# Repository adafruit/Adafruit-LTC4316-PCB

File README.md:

## Adafruit LTC4316 I2C Address Translator - Stemma QT / Qwiic PCB

<a href="http://www.adafruit.com/products/5914"><br/>
Click here to purchase one from the Adafruit shop</a>

PCB files for the Adafruit LTC4316 I2C Address Translator - Stemma QT / Qwiic. 

Format is EagleCAD schematic and board layout
* https://www.adafruit.com/product/5914

### Description

Adafruit has hundreds of designs that use I2C - a two-wire protocol that can let you quickly connect sensors, OLEDs, GPIO expanders, and more. Folks love I2C because you can simply connect 4 wires for power and data, and even better, share those wires with multiple devices!

One things folks don't like about I2C is that each device requires it's own unique 'address'. You can only have one device with a 0x20 address, for example, so while in theory you could have up to 127 device, each for the 7-bits of address space available, in reality you will quickly bump into two sensors with the same address. Many I2C components have jumpers or switches that allow changing the address, but not all. And some only let you pick between two values. One solution is to use an I2C multiplexer,  and these work pretty well, but they require some noodling in your code to set up the 'plexer and then switch between the devices being plexed.

The Adafruit LTC4316 I2C Address Translator is another solution, with some magic sprinkled inside. This chip does on the fly address translation. There's an 'input I2C' half, and an 'output I2C' half. And any devices on the 'output' half will automatically have their addresses translated from the input half. Specifically, each device will have bit A6 flipped  (most-significant-bit of the address) and then bits A4 and A5 can also be flipped or kept the same, with the two DIP switches on board. To determine the translated address, we use XOR bitwise math.

OK that's a little confusing so let's work through an example. Say we have an AHT20 connected on the output side of this breakout. The AHT20 does not have an adjustable I2C address: it's fixed at 0x38. If both DIP switches are ON, then only A6 is flipped. That means the I2C controller on the input side will see 0x38 XOR 0x40 = 0x78 address. If we flip the A5 switch off, now it will be 0x38 XOR 0x60 = 0x58 and if both switches are off, now bits A4, A5 and A6 will be flipped, so 0x38 XOR 0x70 = 0x48. As far as the AHT20 is concerned, it will happily still see I2C writes and reads on 0x38, but from the I2C controller's perspective, the device is responding on the new address.

If you need more than 4 address translation options (two switches give you 4 options) we also have a spot where you can solder an XOR_LOW resistor for setting the 'bottom' 3 bits by soldering in a resistor value according to the datasheet. It can get confusing quickly so we definitely recommend using an I2C scanner to debug. Note also that you have to reset the LTC if you change the translation address with resistors or the DIP switches: the translation value is picked up on chip boot and isn't on-the-fly adjustable without a toggle of the Enable pin.

While this chip is magical, there's a few things to watch for: it doesn't seem to support clock-stretching so not for funky chips like BNO055. Just because you can change the address on the fly, doesn't mean the drive supports it! Some firmware is expecting a specific address and it may not be trivial to change the address. Check the driver to make sure you know how to change the address, to the new value.

To get you going fast, we spun up a custom-made PCB in the STEMMA QT form factor, making it easy to interface. The STEMMA QT connectors on either side are compatible with the SparkFun Qwiic I2C connectors. This allows you to make solderless connections between your development board and the LTC4316 or to chain it with a wide range of other sensors and accessories using a compatible cable. QT Cable is not included, but we have a variety in the shop. 

### License

Adafruit invests time and resources providing this open source design, please support Adafruit and open-source hardware by purchasing products from [Adafruit](https://www.adafruit.com)!

Designed by Limor Fried/Ladyada for Adafruit Industries.

Creative Commons Attribution/Share-Alike, all text above must be included in any redistribution. 
See license.txt for additional details.

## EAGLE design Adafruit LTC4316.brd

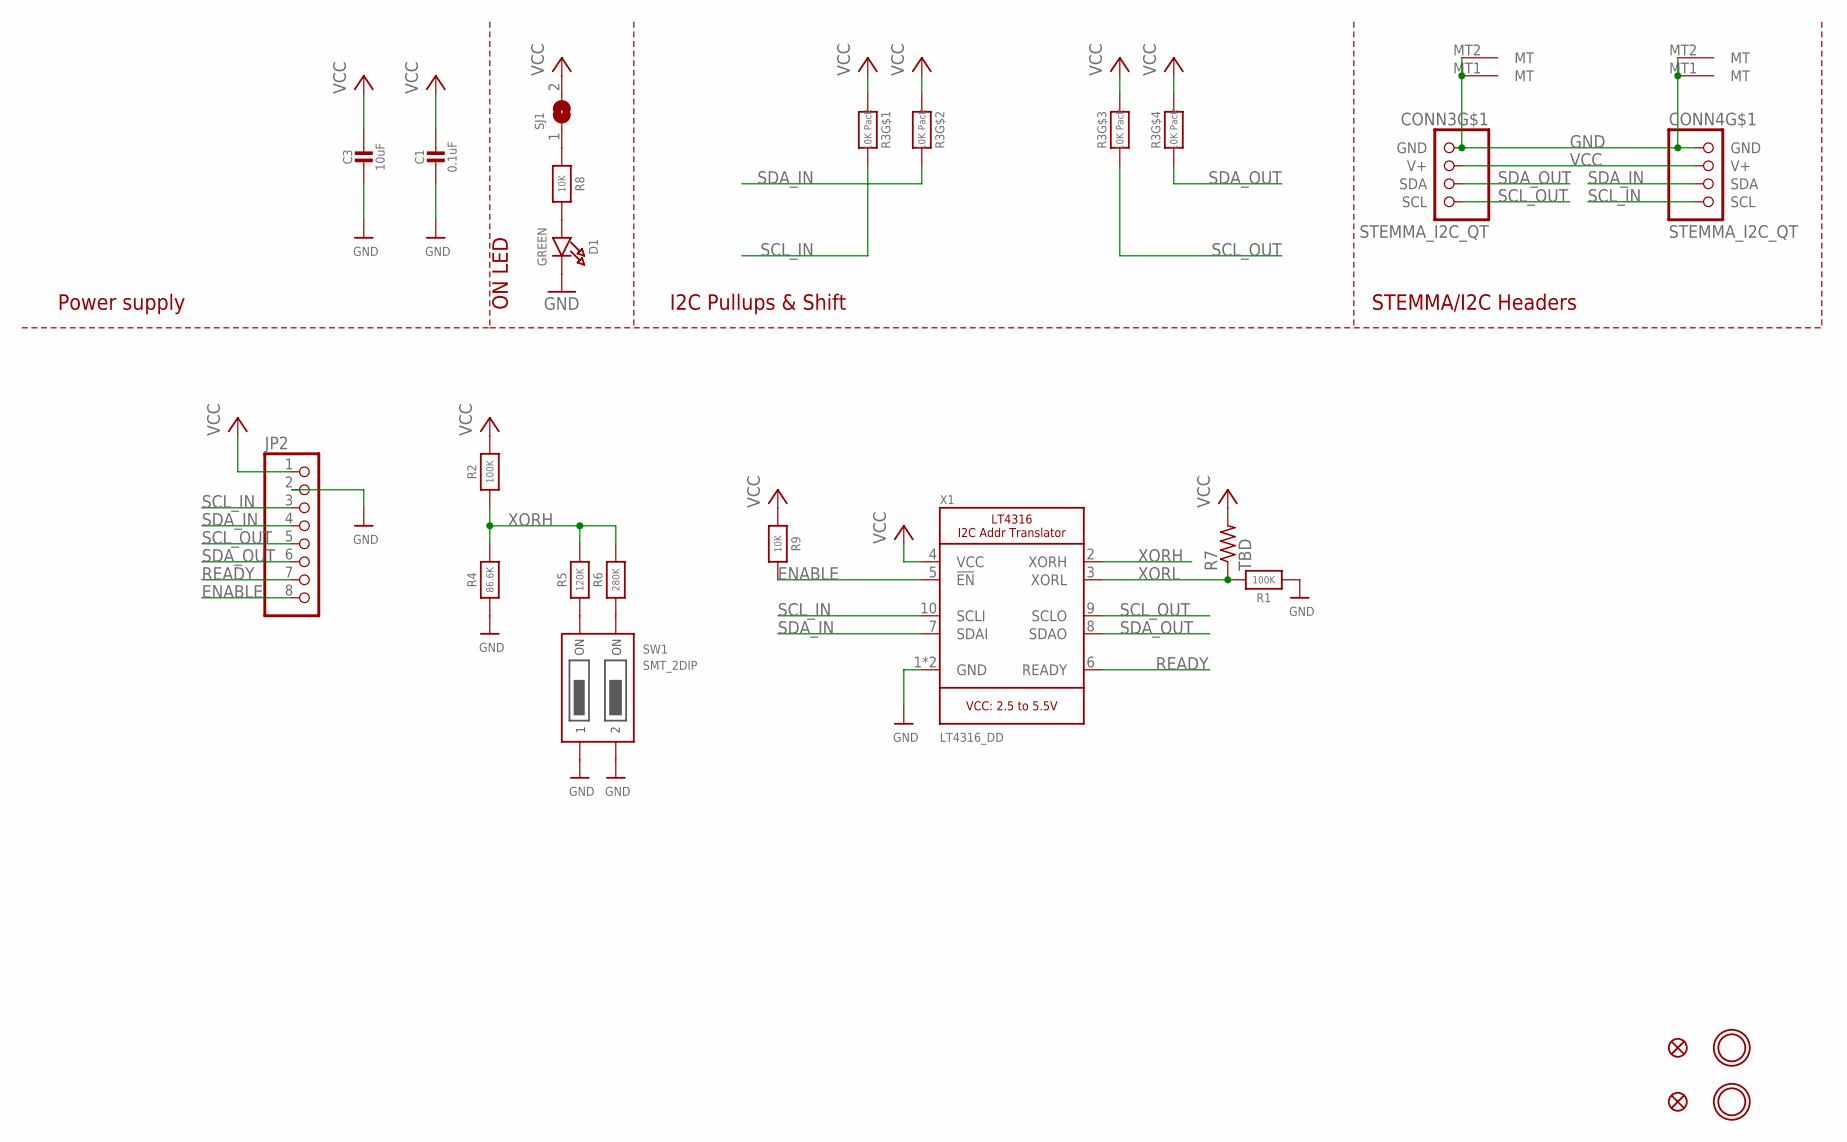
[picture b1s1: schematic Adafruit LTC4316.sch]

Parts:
C1: 0.1uF; 0603-NO
C3: 10uF; 0805-NO
CONN3, CONN4: STEMMA_I2C_QT; JST_SH4
D1: GREEN; CHIPLED_0603_NOOUTLINE
FID3, FID4: FIDUCIAL_1MM
JP2: HEADER-1X870MIL; 1X08_ROUND_70
R1, R2: 100K; 0603-NO
R3: 10K Pack; RESPACK_4X0603
R4: 86.6K; 0603-NO
R5: 120K; 0603-NO
R6: 280K; 0603-NO
R7: TBD; 0204/7
R8, R9: 10K; 0603-NO
SJ1: SOLDERJUMPERCLOSED; SOLDERJUMPER_CLOSEDWIRE
SW1: SMT_2DIP; DIPSWITCH_2PIN
U$1, U$17: MOUNTINGHOLE2.5; MOUNTINGHOLE_2.5_PLATED
X1: LT4316_DD; DFN10_3X3MM

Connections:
ENABLE: JP2.8, R9.2, X1.5 (!EN)
GND: C1.2, C3.2, CONN3.1 (GND), CONN3.MT1 (MT), CONN3.MT2 (MT), CONN4.1 (GND), CONN4.MT1 (MT), CONN4.MT2 (MT), D1.C, JP2.2, R1.1, R4.1, SW1.1OFF, SW1.2OFF, X1.1 (GND), X1.GND
unnamed: D1.A, R8.2
unnamed: R8.1, SJ1.1
unnamed: R5.1, SW1.1ON
unnamed: R6.1, SW1.2ON
READY: JP2.7, X1.6 (READY)
SCL_IN: CONN4.4 (SCL), JP2.3, R3.8 (2), X1.10 (SCLI)
SCL_OUT: CONN3.4 (SCL), JP2.5, R3.3 (1), X1.9 (SCLO)
SDA_IN: CONN4.3 (SDA), JP2.4, R3.7 (2), X1.7 (SDAI)
SDA_OUT: CONN3.3 (SDA), JP2.6, R3.4 (1), X1.8 (SDAO)
VCC: C1.1, C3.1, CONN3.2 (V+), CONN4.2 (V+), JP2.1, R2.2, R3.1, R3.2 (1), R3.5 (2), R3.6 (2), R7.2, R9.1, SJ1.2, X1.4 (VCC)
XORH: R2.1, R4.2, R5.2, R6.2, X1.2 (XORH)
XORL: R1.2, R7.1, X1.3 (XORL)

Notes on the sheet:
I2C Pullups & Shift
STEMMA/I2C Headers
ON LED
Power supply

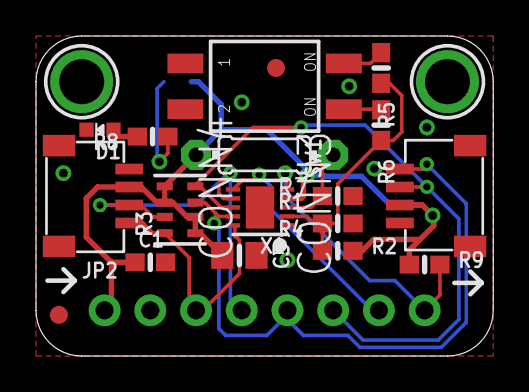
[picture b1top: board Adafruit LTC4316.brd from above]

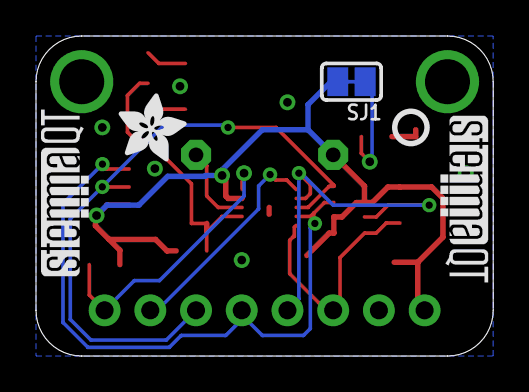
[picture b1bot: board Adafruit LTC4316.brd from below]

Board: 2 copper layers, 25.4 x 17.8 mm, 43 parts (10 on the bottom side), 14 nets.

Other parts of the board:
PLABEL0: PLABEL0
PLABEL1: PLABEL1
PLABEL2: PLABEL2
PLABEL3: PLABEL3
PLABEL4: PLABEL4
PLABEL5: PLABEL5
PLABEL6: PLABEL6
PLABEL7: PLABEL7
PLABEL8: PLABEL8
PLABEL9: PLABEL9
PLABEL10: PLABEL10
PLABEL11: PLABEL11
PLABEL12: PLABEL12
PLABEL13: PLABEL13
PLABEL14: PLABEL14
PLABEL15: PLABEL15
PLABEL16: PLABEL16
U$22: ADAFRUIT_3.5MM
U$25: PCBFEAT-REV-040
U$30, U$31: STEMMAQT

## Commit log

2024-04-02 cookiecutter

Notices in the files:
parts and their libraries:
microbuilder: This work is placed in the public domain, and may be freely used for commercial and non-commercial work with the following conditions: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
